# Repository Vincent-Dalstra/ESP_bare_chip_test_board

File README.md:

# ESP32 bare-chip test board / GPIB interface  #

This board primarily served as a practice design, to see if I could make a functioning esp32-s3 chip based circuit (not module!).
However, I prefer my boards to have a useful purpose rather than just being a paperweight, so decided to combine it with something else I was working on, which was to make an integrated verison of the boards in
https://github.com/Vincent-Dalstra/ESP32-GPIB-pcb, which saves having to use dev boards for this.

The code that it's expected to run can be found at https://github.com/douardda/AR488-ESP32
It is a very useful project, which allows an ESP32 to control various old (and new!) test-equipment.

## Features ##

* Versatile power-input options
  * USB-C port
  * Choice of barrel-jack or 5.08mm screw terminals
    * Works with either polarity - bridge rectifier
    * 3-17V input range
  * If both USB-C and another source are provided, the higher-voltage will be used.
* Wired or Wireless network connectivity
  * Slot for SPI Ethernet adapter (USR-ES1, based on W5500 chip)
  * WiFi/Bluetooth Antenna
* Non-volatile storage
  * 16MB flash via high-speed QIO connection
    * Used to store program code
    * Excess can be used for other purposes
  * 16MB flash via SPI bus
    * Shares the bus with Ethernet adapter
* Programmeable via USB-C port or (optional) 6pin UART header
* Connectors:
  * 24pin connector for GPIB, with 16 IO pins OR
    * alternatively a 10pin 2.50mm JST connector (8x IO, 5V, Gnd)
  * 4pin 1.00mm Piicodev-compatible connector
  * 4pin 2.50mm JST (2x IO, 5V, Gnd)
* Misc.
  * 2x Yellow Indicator LED's
  * 2x Test points that can be soldered to.

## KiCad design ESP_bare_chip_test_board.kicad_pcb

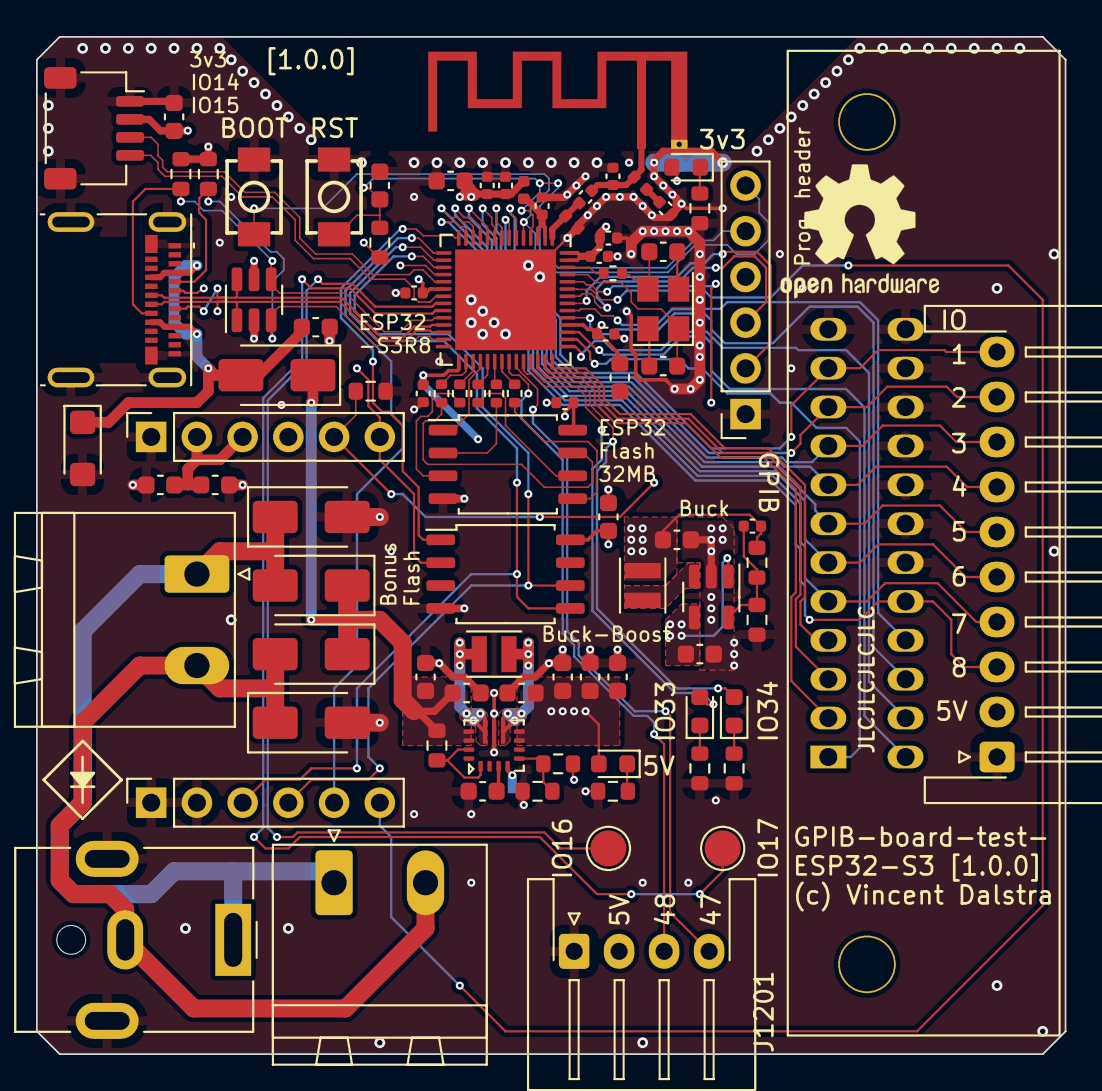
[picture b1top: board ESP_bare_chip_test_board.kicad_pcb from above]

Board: 4 copper layers, 57.1 x 56.5 mm, 90 parts (1 on the bottom side), 79 nets.

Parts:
C201, C1401: 100nF/50V; C_0603_1608Metric
C203, C1003, C1301, C1302, C1402: 22uF/6.3V; C_0603_1608Metric
C301, C302: 10pF; C_0603_1608Metric
C303, C1001, C1004, C1005, C1006, C1007: 10uF/10V; C_0603_1608Metric
C304, C305, C307: 1uF; C_0402_1005Metric
C306, C309, C310, C311, C312: 0.1uF; C_0402_1005Metric
C308: 10nF; C_0402_1005Metric
C401: 4.7pF; C_0402_1005Metric
C402: 2.7pF; C_0402_1005Metric
C403: TBD; C_0402_1005Metric
C501, C1010, C1011: 10uF/25v; C_0603_1608Metric
C1002: 22pF; C_0402_1005Metric
C1012: 100nF; C_0603_1608Metric
D101, D102: YELLOW; LED_0603_1608Metric
D201, D507: GREEN; LED_0603_1608Metric
D501: SMF5V0A; D_SMF
D502, D503, D504, D505, D509: SS210; D_SMA
E401: ANTENNA-GROUNDEDTRACE-15.2MM; Texas_SWRA117D_2.4GHz_Left
J201, J1301, J1302: Conn_01x06; PinSocket_1x06_P2.54mm_Vertical
J501: Barrel_Jack; BarrelJack_CUI_PJ-063AH_Horizontal
J502: PWR_IN; Ningbo_Xinlaiya_XY2500R-D-5.08-2P_1x02_P5.08mm_Horizontal
J503: ALTERNATE; Ningbo_Xinlaiya_XY2500R-D-5.08-2P_1x02_P5.08mm_Horizontal
J801: USB_C_Receptacle; USB_C_Receptacle_Molex_105450-0101
J1101: Conn_01x04; JST_XH_S4B-XH-A-1_1x04_P2.50mm_Horizontal
J1201: NorComp - 112-024-113RYY1; CENTRONICS-24
J1303: Conn_01x10; JST_XH_S10B-XH-A-1_1x10_P2.50mm_Horizontal
J1501: Conn_01x04; JST_SH_SM04B-SRSS-TB_1x04-1MP_P1.00mm_Horizontal
L301: 2.0nH(0.1nH); L_0402_1005Metric
L401: 1.6nH; L_0402_1005Metric
L402: TBD; L_0402_1005Metric
L1001: 2.2uH; L_Changjiang_FNR252012S
L1003: 1.5uH; L_Changjiang_FNR252012S
NT901: NetTie_2; NetTie-2_SMD_Pad0.5mm
Q301: 40MHz; Crystal_SMD_3225-4Pin_3.2x2.5mm
R101, R102, R201, R202: 10kΩ; R_0603_1608Metric
R301: 24nH; R_0402_1005Metric
R302, R303, R304, R305, R306: 0; R_0402_1005Metric
R506, R1002: 33kΩ; R_0603_1608Metric
R601, R602: 5.1kΩ; R_0603_1608Metric
R1001: 150kΩ; R_0603_1608Metric
R1003: 100kΩ; R_0603_1608Metric
R1004: 680kΩ; R_0603_1608Metric
R1005: 130kΩ; R_0603_1608Metric
R1301: 1.5kΩ; R_0603_1608Metric
SW201, SW202: SW_Push; SW_PUSHBUTTON_2PIN_SMD_3×4×2.0
TP104, TP105: TestPoint; TestPoint_Pad_D2.0mm
U301, U1401: W25Q128JVS; SOIC-8_5.23x5.23mm_P1.27mm
U302: ESP32-S3R8; QFN-56-1EP_7x7mm_P0.4mm_EP5.6x5.6mm
U801: D1213A-04TS-7; TSOT-23-6
U1001: TLV62569DBV; SOT-23-5
U1002: TPS63070; VQFN-15-HR_2.5x3mm_P0.5mm

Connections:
+3V3: C203.1, C303.1, C304.1, C305.1, C306.1, C308.1, C311.1, C312.1, C1002.1, C1003.1, C1301.1, C1302.1, C1401.1, C1402.1, D201.2 (A), J201.4, J1302.2, J1302.3, J1501.2, L301.1, L1001.2, R201.1, R1001.1, U302.20 (VDD3P3_RTC), U302.46 (VDD3P3_CPU), U302.55 (VDDA), U302.56 (VDDA), U801.5 (VBUS), U1401.8 (VCC)
+5V: C1001.1, C1004.1, C1005.1, C1006.1, C1007.1, D507.2 (A), J1101.2, J1303.2, R1004.1, U1001.1 (EN), U1001.4 (VIN), U1002.7 (VOUT), U1002.8 (VOUT)
/CLK: J1301.4, U302.17 (GPIO12/ADC2_CH1), U1401.6 (CLK)
/ESP32-S3/ESP32-S3-core/RF: C401.1, L401.1, U302.1 (LNA_IN/RF)
/ESP32-S3/ESP32-S3-core/SPICLK: R304.1, U301.6 (CLK)
/ESP32-S3/ESP32-S3-core/SPICS0: U301.1 (~CS), U302.32 (SPICS0/GPIO29)
/ESP32-S3/ESP32-S3-core/SPID: R306.1, U301.5 (DI(IO0))
/ESP32-S3/ESP32-S3-core/SPIHD: R302.1, U301.7 (IO3)
/ESP32-S3/ESP32-S3-core/SPIQ: R305.1, U301.2 (DO(IO1))
/ESP32-S3/ESP32-S3-core/SPIWP: R303.1, U301.3 (IO2)
/ESP32-S3/ESP32-S3-core/VDD_SPI: C307.1, C310.1, U301.8 (VCC), U302.29 (VDD_SPI)
/ESP32-S3/ESP32-S3-core/antenna_experimental/50Ω ANT: C401.2, C402.1, E401.1 (A), L402.1
/ESP32-S3/ESP_BOOT: J201.6, SW201.2, U302.5 (GPIO0/BOOT)
/ESP32-S3/ESP_EN: C201.1, J201.5, R201.2, SW202.2, U302.4 (CHIP_PU/RESET)
/ESP32-S3/IO1: J1201.11, J1303.10, U302.6 (GPIO1/ADC1_CH0)
/ESP32-S3/IO2: J1201.10, J1303.9, U302.7 (GPIO2/ADC1_CH1)
/ESP32-S3/IO3: J1201.9, J1303.8, U302.8 (GPIO3/ADC1_CH2)
/ESP32-S3/IO4: J1201.8, J1303.7, U302.9 (GPIO4/ADC1_CH3)
/ESP32-S3/IO5: J1201.7, J1303.6, U302.10 (GPIO5/ADC1_CH4)
/ESP32-S3/IO6: J1201.6, J1303.5, U302.11 (GPIO6/ADC1_CH5)
/ESP32-S3/IO7: J1201.5, J1303.4, U302.12 (GPIO7/ADC1_CH6)
/ESP32-S3/IO8: J1201.17, J1303.3, U302.13 (GPIO8/ADC1_CH7)
/ESP32-S3/IO14: J1501.3, U302.19 (GPIO14/ADC2_CH3)
/ESP32-S3/IO15: J1501.4, U302.21 (GPIO15/ADC2_CH4/XTAL_32K_P)
/ESP32-S3/IO16: TP105.1, U302.22 (GPIO16/ADC2_CH5/XTAL_32K_N)
/ESP32-S3/IO17: TP104.1, U302.23 (GPIO17/ADC2_CH6)
/ESP32-S3/IO33: D101.2 (A), U302.38 (GPIO33)
/ESP32-S3/IO34: D102.2 (A), U302.39 (GPIO34)
/ESP32-S3/IO35: J1201.2, U302.40 (GPIO35)
/ESP32-S3/IO36: J1201.3, U302.41 (GPIO36)
/ESP32-S3/IO37: J1201.4, U302.42 (GPIO37)
/ESP32-S3/IO38: J1201.14, U302.43 (GPIO38)
/ESP32-S3/IO39: J1201.1, U302.44 (MTCK/JTAG/GPIO39)
/ESP32-S3/IO40: J1201.13, U302.45 (MTDO/JTAG/GPIO40)
/ESP32-S3/IO41: J1201.15, U302.47 (MTDI/JTAG/GPIO41)
/ESP32-S3/IO42: J1201.16, U302.48 (MTMS/JTAG/GPIO42)
/ESP32-S3/UART0_Rx: J201.3, U302.50 (U0RXD/PROG/GPIO44)
/ESP32-S3/UART0_Tx: J201.2, U302.49 (U0TXD/PROG/GPIO43)
/ETH_RST: J1302.5, R1301.2, U302.52 (GPIO46)
/IO47: J1101.4, U302.37 (SPICLK_P/GPIO47)
/IO48: J1101.3, U302.36 (SPICLK_N/GPIO48)
/MISO: J1302.6, U302.18 (GPIO13/ADC2_CH2), U1401.2 (DO(IO1))
/MOSI: J1301.3, U302.16 (GPIO11/ADC2_CH0), U1401.5 (DI(IO0))
/Power/VBUS: C501.1, D501.1 (A1), D509.2 (A), J801.A4 (VBUS), J801.A9 (VBUS), J801.B4 (VBUS), J801.B9 (VBUS)
/Power/V_{IN}: C1010.1, C1011.1, D502.1 (K), D503.1 (K), D509.1 (K), R1003.1, U1002.12 (VIN), U1002.13 (VIN)
/Power/V_{IN}_Left: D502.2 (A), D504.1 (K), J501.1, J502.1, J503.1
/Power/V_{IN}_Right: D503.2 (A), D505.1 (K), J501.2, J502.2, J503.2
/Power/buck-boost-5v/EN_{reg}: R1003.2, U1002.1 (PS/SYNC), U1002.14 (EN)
/Power/buck-boost-5v/FB: R1004.2, R1005.1, U1002.5 (FB)
/Power/buck-boost-5v/L1: L1003.1, U1002.11 (L1)
/Power/buck-boost-5v/L2: L1003.2, U1002.9 (L2)
/Power/buck-boost-5v/SGND: NT901.1, U1002.4 (GND)
/Power/buck-boost-5v/V_{AUX}: C1012.1, U1002.3 (VAUX)
/Power/step-down-5v-3v3_ESP32/FB: C1002.2, R1001.2, R1002.1, U1001.5 (FB)
/Power/step-down-5v-3v3_ESP32/SW: L1001.1, U1001.3 (SW)
/USB/CC1: J801.A5 (CC1), R602.2, U302.27 (GPIO21), U801.3 (I/O2)
/USB/CC2: J801.B5 (CC2), R601.2, U302.24 (GPIO18/ADC2_CH7), U801.4 (I/O3)
/USB_D+: J801.A6 (D+), J801.B6 (D+), U302.26 (GPIO20/USB_D+/ADC2_CH9), U801.1 (I/O1)
/USB_D-: J801.A7 (D-), J801.B7 (D-), U302.25 (GPIO19/USB_D-/ADC2_CH8), U801.6 (I/O4)
/~ETH_CS0: J1301.5, U302.15 (GPIO10/ADC1_CH9)
/~ETH_INT: J1301.6, U302.51 (GPIO45)
/~FRAM_CS: U302.14 (GPIO9/ADC1_CH8), U1401.1 (~CS)
GND: C201.2, C203.2, C303.2, C304.2, C305.2, C306.2, C307.2, C308.2, C309.2, C310.2, C311.2, C312.2, C402.2, C403.2, C501.2, C1001.2, C1003.2, C1004.2, C1005.2, C1006.2, C1007.2, C1010.2, C1011.2, C1012.2, C1301.2, C1302.2, C1401.2, C1402.2, D501.2 (A2), D504.2 (A), D505.2 (A), E401.2 (Shield), J201.1, J501.MP (MountPin), J801.A1 (GND), J801.A12 (GND), J801.B1 (GND), J801.B12 (GND), J801.S1 (SHIELD), J1101.1, J1201.12, J1201.18, J1201.19, J1201.20, J1201.21, J1201.22, J1201.23, J1201.24, J1301.1, J1301.2, J1302.1, J1303.1, J1501.1, J1501.MP (MountPin), L401.2, NT901.2, R101.2, R102.2, R202.2, R506.2, R601.1, R602.1, R1002.2, R1005.2, R1301.1, SW201.1, SW202.1, U301.4 (GND), U302.57 (GND), U801.2 (GND), U1001.2 (GND), U1002.10 (PGND), U1401.4 (GND)
unnamed: C301.2, Q301.4
unnamed: C302.1, Q301.3, R301.1
unnamed: C302.2, Q301.2
unnamed: C403.1, L402.2
unnamed: D101.1 (K), R101.1
unnamed: D102.1 (K), R102.1
unnamed: D201.1 (K), R202.1
unnamed: D507.1 (K), R506.1
unnamed: R304.2, U302.33 (SPICLK/GPIO30)
unnamed: R306.2, U302.35 (SPID/GPIO32)
unnamed: R302.2, U302.30 (SPIHD/GPIO27)
unnamed: R305.2, U302.34 (SPIQ/GPIO31)
unnamed: R303.2, U302.31 (SPIWP/GPIO28)
unnamed: C301.1, Q301.1, U302.53 (XTAL_N)
unnamed: R301.2, U302.54 (XTAL_P)
VDD3P3: C309.1, L301.2, U302.2 (VDD3P3), U302.3 (VDD3P3)

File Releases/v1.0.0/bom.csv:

Comment,Designator,Footprint,LCSC
10kΩ,"R101,R102,R201,R202",Resistor_SMD:R_0603_1608Metric,C25804
YELLOW,"D101,D102",LED_SMD:LED_0603_1608Metric,C72038
22uF/6.3V,"C203,C1003,C1301,C1302,C1402",Capacitor_SMD:C_0603_1608Metric,C59461
Conn_01x04,J1501,Connector_JST:JST_SH_SM04B-SRSS-TB_1x04-1MP_P1.00mm_Horizontal,C145956
100nF/50V,"C201,C1401",Capacitor_SMD:C_0603_1608Metric,C14663
GREEN,"D201,D507",LED_SMD:LED_0603_1608Metric,C779453
SW_Push,"SW201,SW202",Button_Switch_SMD_custom:SW_PUSHBUTTON_2PIN_SMD_3×4×2.0,C720477
1uF,"C304,C305,C307",Capacitor_SMD:C_0402_1005Metric,C52923
40MHz,Q301,Crystal:Crystal_SMD_3225-4Pin_3.2x2.5mm,C379787
10pF,"C301,C302",Capacitor_SMD:C_0603_1608Metric,C1634
0,"R302,R303,R304,R305,R306",Resistor_SMD:R_0402_1005Metric,C203078
10nF,C308,Capacitor_SMD:C_0402_1005Metric,C15195
W25Q128JVS,"U301,U1401",Package_SO:SOIC-8_5.23x5.23mm_P1.27mm,C97521
2.0nH(0.1nH),L301,Inductor_SMD:L_0402_1005Metric,C43365
0.1uF,"C306,C309,C310,C311,C312",Capacitor_SMD:C_0402_1005Metric,C307331
10uF/10V,"C303,C1001,C1004,C1005,C1006,C1007",Capacitor_SMD:C_0603_1608Metric,C19702
24nH,R301,Resistor_SMD:R_0402_1005Metric,C330863
ESP32-S3R8,U302,Package_DFN_QFN:QFN-56-1EP_7x7mm_P0.4mm_EP5.6x5.6mm,C2913194
1.6nH,L401,Inductor_SMD:L_0402_1005Metric,C162539
4.7pF,C401,Capacitor_SMD:C_0402_1005Metric,C1569
2.7pF,C402,Capacitor_SMD:C_0402_1005Metric,C1561
SS210,"D502,D503,D504,D505,D509",Diode_SMD:D_SMA,C14996
SMF5V0A,D501,Diode_SMD:D_SMF,C2905637
10uF/25v,"C501,C1010,C1011",Capacitor_SMD:C_0603_1608Metric,C96446
33kΩ,"R506,R1002",Resistor_SMD:R_0603_1608Metric,C4216
680kΩ,R1004,Resistor_SMD:R_0603_1608Metric,C25822
130kΩ,R1005,Resistor_SMD:R_0603_1608Metric,C22795
100nF,C1012,Capacitor_SMD:C_0603_1608Metric,C14663
TPS63070,U1002,Package_DFN_QFN_custom:VQFN-15-HR_2.5x3mm_P0.5mm,C109322
100kΩ,R1003,Resistor_SMD:R_0603_1608Metric,C25803
1.5uH,L1003,Inductor_SMD:L_Changjiang_FNR252012S,C5832371
2.2uH,L1001,Inductor_SMD:L_Changjiang_FNR252012S,C5832372
22pF,C1002,Capacitor_SMD:C_0402_1005Metric,C1555
150kΩ,R1001,Resistor_SMD:R_0603_1608Metric,C22807
TLV62569DBV,U1001,Package_TO_SOT_SMD:SOT-23-5,C141836
1.5kΩ,R1301,Resistor_SMD:R_0603_1608Metric,C22843 
D1213A-04TS-7,U801,Package_TO_SOT_SMD:TSOT-23-6,C460588
5.1kΩ,"R601,R602",Resistor_SMD:R_0603_1608Metric,C23186
USB_C_Receptacle,J801,Connector_USB:USB_C_Receptacle_Molex_105450-0101,C134092

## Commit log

2023-12-12 Create from 4l template, copy in existing design
    Intent is to test the ESP32-S3 and ESP32-C3 bare chips (with qio flash
    IC and clock chip connected). If it works, it would greatly reduce the
    price of small-batch boards (because ESP32 modules cannot be placed in
    JLCPCB's economic assembly).
    Was already working on a design using an ESP32-S3 bare chip, so have
    copied int ehr elevant parts of that.
2024-03-27 Copy in component arrangement from SDMMC test design
    Already had an efficient arrangement for the SPI flash chip, Clock
    crystal, and Antenna.
2024-03-27 squash! Copy in component arrangement from SDMMC test design
    Using it as a template.
2024-03-28 Add ESP32-C3 subsheet. SMall corrections
    Add and wire up ESP32-C3-Mini on a subsheet, and note down which pins
    are used for strapping etc. This will then be replaced with a bare-chip
    ESP32-C3 circuit, much like with the existing ESP32-S3 circuit.
2024-03-30 Add sheet for ESP32-C3 bare chip as well.
    Similar to the ESP32-S3 circuit, so I copied most of it (one capacitor
    is not needed, according to the reference schematics).
    No flash chip is attached; makes sense to use one of the embedded flash
    chips to test with, as it makes for a very small design (and 16MB is
    really not needed).
2024-04-07 Add 5v and 3v3 buck regulators, brige rectifier
    Buck regulators are copied from existing designs. 5V regulator needs to
    be reworked though; due to ESD vulnerability.
    Added 4 diodes in bridge rectifier configuration. Provides a simpler
    solution than the polarity-protected eFuse. Due to how the
    buck-regulators work, it should be fine for any voltage from ~4.8V 17V
    (max Vin of buck regulator). Downside is icnreased power-dissipation,
2024-04-18 PCB changes, added useful connectors
    Added a whole bunch of things that should make it useful - e.g.
    ethernet, an extra flash chip for general storage, piicodev connectors
    for I2C.
    Also added a GPIB connector footprint; dev-board version worked nicely,
    but may as well make this work for that too. Saves bying dev boards : )
2024-04-18 Add barrel jack to schematic
2024-05-07 Uknown changes?File formats?
2024-05-13 Unknown changes? Arranging components, I believe
2024-05-13 Apply XOR to 5V buck reg and USB power
    Some 5V regulators will be very unhappy if a higher-voltage is applied -
    e.g. from USB. Therefore, use a comparator to turn off the load-switch
    when 12V power is present.
    Circuit got a bit more complex because it needs to deal with dynamic
    situations as things are plugged in. Will still need some work, likely.
2024-05-19 Replace buck-regulator with buck-boost regulator
    Replaced the buck-regulator with a buck-boost regulator. The primary
    purpose is because the buck-regulator could fail when a higher-voltage
    output was conected. The buck-regulators internal switches and design
    should be much less vulnerable for this.
    A second benefit of the buck-boost regulator is thata 5V input can now
    still be used, as it accounts for the voltage-drop from the
2024-05-19 Removed complex OR'ing circuit
    Replaced it with a simple one that will turn off the USB 5V switch when
    the buck-regulator is providing power (using PGOOD pin to signal this).
    May not even be necessary, but good to have.
2024-05-19 Arranged buck-boost regulator. Moved some components slightly.
2024-05-23 Removed USB-PD circuit - simplifies board
2024-05-23 Layed-out 5V buck-boost regulator ciruit
2024-05-23 Planning/wiring up some traces on PCB
2024-05-23 Picked part numbers and placed most remaining MCU support components
2024-05-28 Started wiring up traces
2024-05-28 Fixup ESP flash memory wiring
    One of the wires was missing, so added it. Rearranged wiring to allow it
    to fit without having to via across layers.
2024-05-28 More wiring - Ethernet, SPI flash
2024-05-28 More wiring - GPIB connector, partially routed
2024-05-30 partial! Ran wires for GPIB connector
2024-06-13 Position final few components
    Removed one ESD diode arrray - experimental board, so not really needed,
    with the exception of the USB lines.
    Add and position 5V indicator LED
    Finished wiring up the 5V buck-boost regulator
2024-06-13 Wire remaining traces, fix DRC errors
2024-06-13 Add test pads for extra IO pins
    Can be soldered to if desired for some testing purpose
2024-06-13 Free up IO26 (to allow for PSRAM)
    Had spare IO lines, so may as well use a different one to do ETH_INT
    instead of IO26.
2024-06-13 Add order codes for all components
2024-06-13 Switch to ESP32-S3R8 (8Mb PSRAM)
    Switch to the ESP32-S3 chip that has integrated PSRAM, so I can test it
    Disadvantage is it means IO26 cannot be used, and is more expensive.
    Still uses external flash chip.
2024-06-13 Add JLCPCB corrections for new components
2024-06-14 Silkscreen work. Edit tittle block/version number
2024-06-23 Final corrections and silkscreen labels
2024-06-23 Ran some simple tests, working well
    Verified that these work:
    - Power-up from USB port
    - Flash and monitor over USB
    - Code on flash is persistent
    - Wifi antenna can communicate at the expected range
    - One of the indicator LED's (for blink)
2024-06-23 Create README.md
    Describe the board as it is now, including its purpose and features.
2025-07-15 Move all subsheets into 'main' subsheet, below root
    Keeping all the subsheets in a dedicated 'subsheet' folder makes things
    much, much neater. However, specifying filepaths for subsheets has an
    interesting problem; they use paths RELATIVE TO THE PARENT SHEET.
    The consequence of is that if a subsheet is part of the root sheet, it
    needs to be prefixed with 'subsheet/', but NOT if it's further down.
    This inconsistency can be resolved by having a single 'main' sheet at
2025-07-15 Remove unused sheets.
    Inherited from a different project used as a template for this one, but
    not used here.
2026-04-12 Update Makefile (improvements)
    Improvements to Makefile scripts over time in other projects.
    - Generate docs as well (schematic, 3D model)
    - Don't generate redundant gerbers.zip
    - Fix dependency relationships between Makefile targets
    - Pinion
2026-04-12 Make all schematic sheets A4
2026-04-12 Add schematics and 3D-model for v1.0.0
    Updated Makefile now creates these automatically, so there's little
    effort required to add them in.
2026-04-12 Add pictures of board (3D-viewer)
2026-04-12 fix (docs): incorrect link in README
